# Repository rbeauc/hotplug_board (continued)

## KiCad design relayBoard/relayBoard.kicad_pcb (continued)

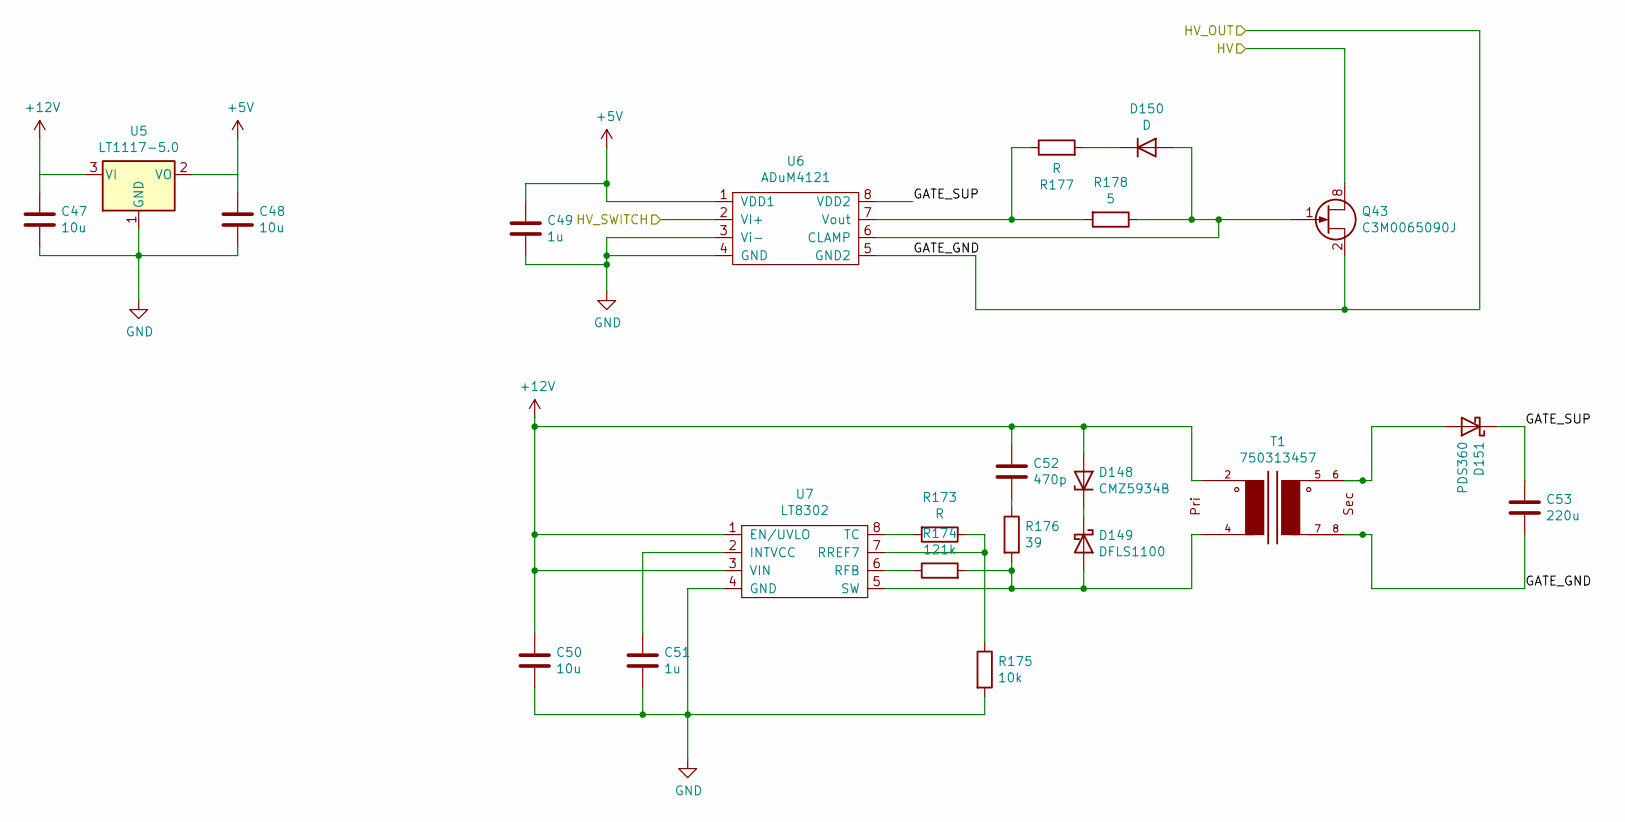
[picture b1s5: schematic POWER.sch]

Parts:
C47, C48, C50: 10u; R_0603_1608Metric
C49, C51: 1u; R_0603_1608Metric
C52: 470p; R_0603_1608Metric
C53: 220u; R_1210_3225Metric
D148: CMZ5934B; D_SMA
D149: DFLS1100; D_PowerDI-123
D150: D; D_0805_2012Metric
D151: PDS360; D_PowerDI-5
Q43: C3M0065090J; Infineon_PG-TO-220-7Lead_TabPin8
R173, R177: R; R_0603_1608Metric
R174: 121k; R_0603_1608Metric
R175: 10k; R_0603_1608Metric
R176: 39; R_0603_1608Metric
R178: 5; R_0603_1608Metric
T1: 750313457; EP10_SMD_H_8PIN_(6052)
U5: LT1117-5.0; SOT-223-3_TabPin2
U6: ADuM4121; SOIC-8_5.23x5.23mm_P1.27mm
U7: LT8302; SO-8_3.9x4.9mm_P1.27mm

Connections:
+5V: C48.1, C49.1, U5.2 (VO), U6.1 (VDD1); also elsewhere on the board
+12V: C47.1, C50.1, C52.1, D148.2 (A), T1.2, U5.3 (VI), U7.1 (EN/UVLO), U7.3 (VIN); also elsewhere on the board
/HV_SW: U6.2 (VI+); also elsewhere on the board
/INPUT_2_IN: Q43.8 (D); also elsewhere on the board
/Sheet5F711699/GATE_SUP: C53.1, D151.1 (K), U6.8 (VDD2)
GND: C47.2, C48.2, C49.2, C50.2, C51.2, R175.2, U5.1 (GND), U6.3 (Vi-), U6.4 (GND), U7.4 (GND); also elsewhere on the board
unnamed: C51.1, U7.2 (INTVCC)
unnamed: C52.2, R176.1
unnamed: D148.1 (K), D149.1 (K)
unnamed: D149.2 (A), R174.2, R176.2, T1.4, U7.5 (SW)
unnamed: D150.1 (K), R177.2
unnamed: D150.2 (A), Q43.1 (G), R178.1, U6.6 (CLAMP)
unnamed: R173.1, R175.1, U7.7 (RREF7)
unnamed: R173.2, U7.8 (TC)
unnamed: R174.1, U7.6 (RFB)
unnamed: R177.1, R178.2, U6.7 (Vout)

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
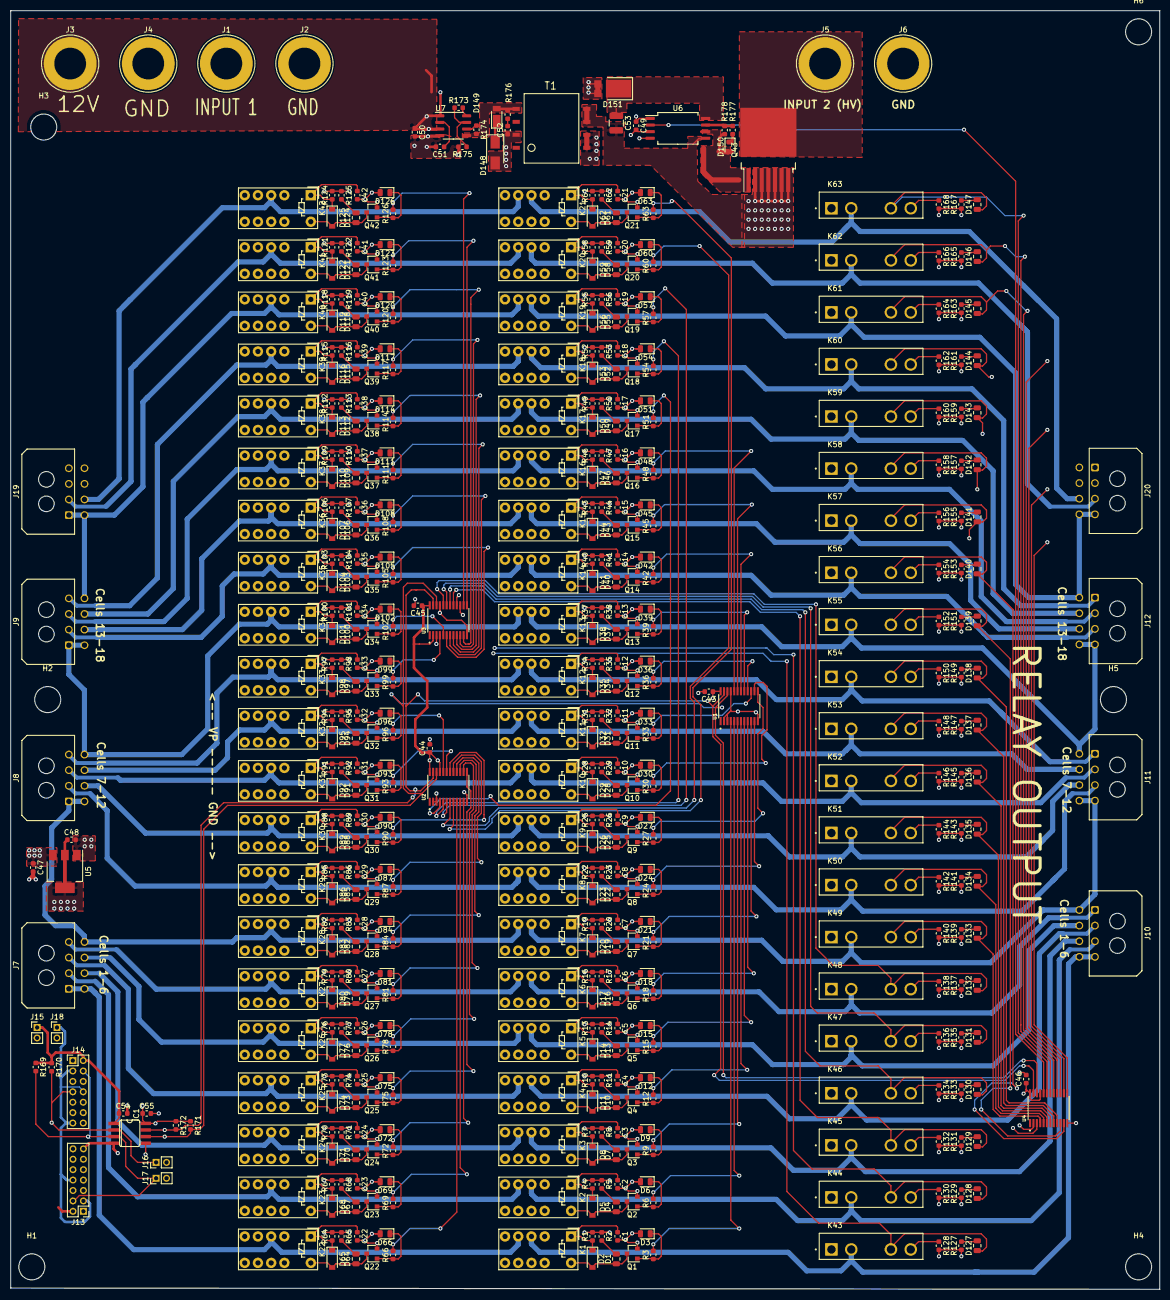
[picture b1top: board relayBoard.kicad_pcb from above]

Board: 4 copper layers, 220.7 x 245.6 mm, 525 parts (0 on the bottom side), 340 nets.

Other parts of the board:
R4, R7, R10, R13, R16, R19, R22, R25, R28, R31, R34, R37, R40, R43, R46, R49, R52, R55, R58, R61, R64, R67, R70, R73, R76, R79, R82, R85, R88, R91, R94, R97, R100, R103, R106, R109, R112, R115, R118, R121, R124: 330; R_0603_1608Metric

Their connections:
+12V: R4.2, R7.2, R10.2, R13.2, R16.2, R19.2, R22.2, R25.2, R28.2, R31.2, R34.2, R37.2, R40.2, R43.2, R46.2, R49.2, R52.2, R55.2, R58.2, R61.2, R64.2, R67.2, R70.2, R73.2, R76.2, R79.2, R82.2, R85.2, R88.2, R91.2, R94.2, R97.2, R100.2, R103.2, R106.2, R109.2, R112.2, R115.2, R118.2, R121.2, R124.2; also elsewhere on the board
unnamed 162: R4.1; also elsewhere on the board
unnamed 163: R7.1; also elsewhere on the board
unnamed 164: R10.1; also elsewhere on the board
unnamed 165: R13.1; also elsewhere on the board
unnamed 166: R16.1; also elsewhere on the board
unnamed 167: R19.1; also elsewhere on the board
unnamed 168: R22.1; also elsewhere on the board
unnamed 169: R25.1; also elsewhere on the board
unnamed 170: R28.1; also elsewhere on the board
unnamed 171: R31.1; also elsewhere on the board
unnamed 172: R34.1; also elsewhere on the board
unnamed 173: R37.1; also elsewhere on the board
unnamed 174: R40.1; also elsewhere on the board
unnamed 175: R43.1; also elsewhere on the board
unnamed 176: R46.1; also elsewhere on the board
unnamed 177: R49.1; also elsewhere on the board
unnamed 178: R52.1; also elsewhere on the board
unnamed 179: R55.1; also elsewhere on the board
unnamed 180: R58.1; also elsewhere on the board
unnamed 181: R61.1; also elsewhere on the board
unnamed 182: R64.1; also elsewhere on the board
unnamed 183: R67.1; also elsewhere on the board
unnamed 184: R70.1; also elsewhere on the board
unnamed 185: R73.1; also elsewhere on the board
unnamed 186: R76.1; also elsewhere on the board
unnamed 187: R79.1; also elsewhere on the board
unnamed 188: R82.1; also elsewhere on the board
unnamed 189: R85.1; also elsewhere on the board
unnamed 190: R88.1; also elsewhere on the board
unnamed 191: R91.1; also elsewhere on the board
unnamed 192: R94.1; also elsewhere on the board
unnamed 193: R97.1; also elsewhere on the board
unnamed 194: R100.1; also elsewhere on the board
unnamed 195: R103.1; also elsewhere on the board
unnamed 196: R106.1; also elsewhere on the board
unnamed 197: R109.1; also elsewhere on the board
unnamed 198: R112.1; also elsewhere on the board
unnamed 199: R115.1; also elsewhere on the board
unnamed 200: R118.1; also elsewhere on the board
unnamed 201: R121.1; also elsewhere on the board
unnamed 202: R124.1; also elsewhere on the board

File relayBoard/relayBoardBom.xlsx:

Id | Designator | Package | Quantity | Designation | Supplier and ref | Column1 | _1
1 | U4,U3,U2,U1 | SOP65P640X110-24N | 4 | PCA9555APW,118
2 | T1 | EP10_SMD_H_8PIN_(6052) | 1 | 750313457
3 | IC1 | SO08 | 1 | ADUM1251
4 | D125,D122,D119,D116,D113,D110,D107,D104,D101,D98,D95,D92,D89,D86,D83,D80,D77,D7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 | D_SOD-123 | 42 | MMSZ5245B-E3-08
5 | D151 | D_PowerDI-5 | 1 | PDS360
6 | D149 | D_PowerDI-123 | 1 | DFLS1100
7 | D148 | D_SMA | 1 | CMZ5934B
8 | J8,J12,J11,J10,J9,J7 | Molex_Micro-Fit_3.0_43045-0800_2x04_P3.00mm_Horizontal | 6 | Conn_02x04_Top_Bottom
9 | C53 | R_1210_3225Metric | 1 | 220u
10 | R178 | R_0603_1608Metric | 1 | 5
11 | R177,R173 | R_0603_1608Metric | 2 | R
12 | R176 | R_0603_1608Metric | 1 | 39
13 | R175 | R_0603_1608Metric | 1 | 10k
14 | R174 | R_0603_1608Metric | 1 | 121k
15 | R172,R171,R170,R169,R125,R122,R119,R116,R113,R110,R107,R104,R101,R98,R95,R92,R8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 | R_0603_1608Metric | 46 | 4.75k
16 | R168,R167,R166,R165,R164,R163,R162,R161,R160,R159,R158,R157,R156,R155,R154,R153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 | R_0603_1608Metric | 42 | 1k
17 | R126,R123,R120,R117,R114,R111,R108,R105,R102,R99,R96,R93,R90,R87,R84,R81,R78,R7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 | R_0603_1608Metric | 42 | 100
18 | R124,R121,R118,R115,R112,R109,R106,R103,R100,R97,R94,R91,R88,R85,R82,R79,R76,R7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 | R_0603_1608Metric | 42 | 330
19 | D150 | D_0805_2012Metric | 1 | D
20 | D147,D146,D145,D144,D143,D142,D141,D140,D139,D138,D137,D136,D135,D134,D133,D132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 | R_0805_2012Metric | 63 | 17-21SUYC/TR8
21 | D126,D123,D120,D117,D114,D111,D108,D105,D102,D99,D96,D93,D90,D84,D78,D72,D66,D6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 | D_0805_2012Metric | 42 | D_Zener
22 | K42,K41,K40,K39,K38,K37,K36,K35,K34,K33,K32,K31,K30,K29,K28,K27,K26,K25,K24,K23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 | Relay_DPDT_Omron_G6SK-2 | 42 | G6S-2 DC12
23 | U7 | SO-8_3.9x4.9mm_P1.27mm | 1 | LT8302
24 | U6 | SOIC-8_5.23x5.23mm_P1.27mm | 1 | ADuM4121
25 | U5 | SOT-223-3_TabPin2 | 1 | LT1117-5.0
26 | Q43 | Infineon_PG-TO-220-7Lead_TabPin8 | 1 | C3M0065090J
27 | Q42,Q41,Q40,Q39,Q38,Q37,Q36,Q35,Q34,Q33,Q32,Q31,Q30,Q29,Q28,Q27,Q26,Q25,Q24,Q23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 | SOT-23 | 42 | 2N7002
28 | K63,K62,K61,K60,K59,K58,K57,K56,K55,K54,K53,K52,K51,K50,K49,K48,K47,K46,K45,K44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 | TO381P2016X515X2916-4 | 21 | CPC1777J
29 | J14,J13 | PinHeader_2x07_P2.00mm_Vertical | 2 | Conn_02x07_Odd_Even
30 | J6,J5,J4,J3,J2,J1 | Banana_Jack_1Pin | 6 | Conn_01x01
31 | H6,H5,H4,H3,H2,H1 | MountingHole_5mm | 6 | MountingHole
32 | C52 | R_0603_1608Metric | 1 | 470p
33 | C51,C49 | R_0603_1608Metric | 2 | 1u
34 | C50,C48,C47 | R_0603_1608Metric | 3 | 10u
35 | C46,C45,C44,C43 | R_0603_1608Metric | 4 | 100n
36 | C42,C41,C40,C39,C38,C37,C36,C35,C34,C33,C32,C31,C30,C29,C28,C27,C26,C25,C24,C23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 | R_0603_1608Metric | 42 | 10n

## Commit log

2020-08-05 initial commit, old relay board design to be modified
2020-08-06 first pass at revisions
2020-08-15 First pass layout finished
2020-08-19 second pass relay board layout
2020-08-20 Third pass, fixing footprints to match JLC components
2020-09-18 Cuyler's revisions to the relay board
2020-10-21 updates to connector connections and converter transformer
